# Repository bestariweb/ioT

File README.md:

# ioT
this Repository contain any tutorials for Arduino, Nodemcu and wemos device
You can find source code for respectively device on the folder by device name

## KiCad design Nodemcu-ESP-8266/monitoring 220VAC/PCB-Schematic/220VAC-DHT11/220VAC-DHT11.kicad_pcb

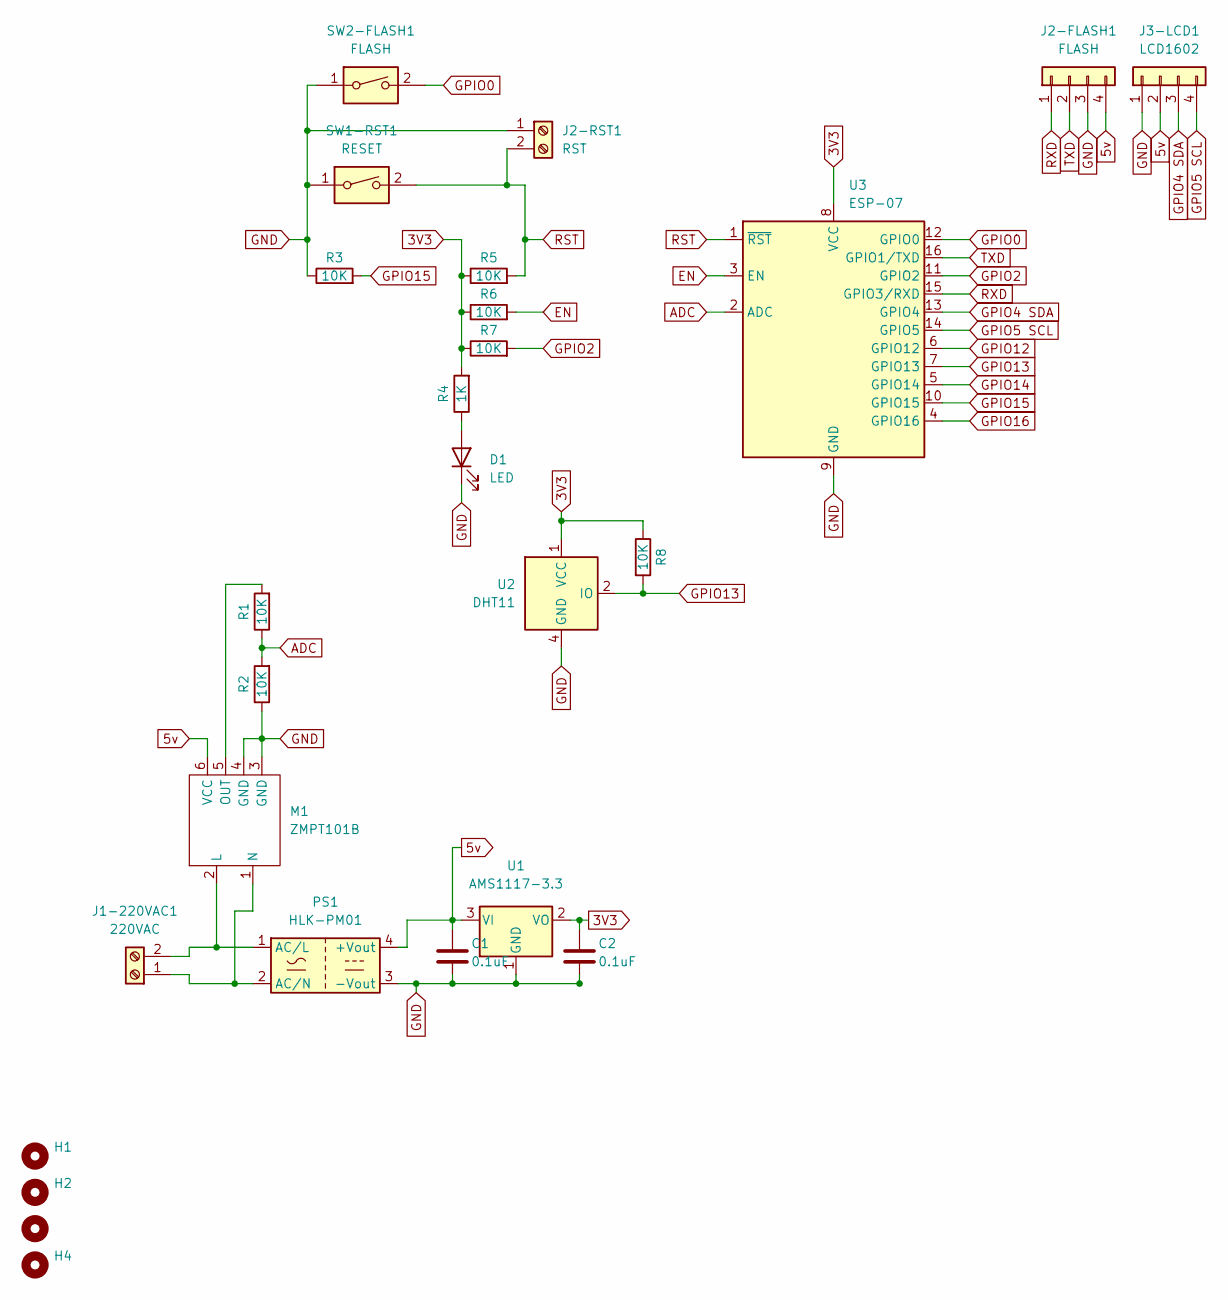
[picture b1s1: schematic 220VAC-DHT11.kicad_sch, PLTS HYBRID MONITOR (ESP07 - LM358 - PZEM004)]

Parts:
C1, C2: 0.1uF; C_1210_3225Metric
D1: LED; LED_D3.0mm_Clear
H1, H2, H3, H4: MountingHole_3.2mm_M3_ISO14580_Pad
J1-220VAC1: 220VAC; TerminalBlock_Phoenix_MKDS-1,5-2_1x02_P5.00mm_Horizontal
J2-FLASH1: FLASH; PinHeader_1x04_P2.54mm_Horizontal
J2-RST1: RST; TerminalBlock_Phoenix_PT-1,5-2-3.5-H_1x02_P3.50mm_Horizontal
J3-LCD1: LCD1602; PinHeader_1x04_P2.54mm_Vertical
M1: ZMPT101B; ZMPT101B_Module
PS1: HLK-PM01; Converter_ACDC_HiLink_HLK-PMxx
R1, R2, R3, R5, R6, R7, R8: 10K; R_1206_3216Metric_Pad1.30x1.75mm_HandSolder
R4: 1K; R_1206_3216Metric_Pad1.30x1.75mm_HandSolder
SW1-RST1: RESET; SW_PUSH_6mm_H7.3mm
SW2-FLASH1: FLASH; SW_PUSH_6mm_H7.3mm
U1: AMS1117-3.3; SOT-223-3_TabPin2
U2: DHT11; Aosong_DHT11_5.5x12.0_P2.54mm
U3: ESP-07

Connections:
3V3: C2.1, R4.2, R5.1, R6.1, R7.1, R8.1, U1.2 (VO), U2.1 (VCC), U3.8 (VCC)
5v: C1.1, J2-FLASH1.4, J3-LCD1.2, M1.6 (VCC), PS1.4 (+Vout), U1.3 (VI)
ADC: R1.1, R2.2, U3.2 (ADC)
EN: R6.2, U3.3 (EN)
GND: C1.2, C2.2, D1.1 (K), J2-FLASH1.3, J2-RST1.1, J3-LCD1.1, M1.3 (GND), M1.4 (GND), PS1.3 (-Vout), R2.1, R3.1, SW1-RST1.1, SW2-FLASH1.1, U1.1 (GND), U2.4 (GND), U3.9 (GND)
GPIO0: SW2-FLASH1.2, U3.12 (GPIO0)
GPIO2: R7.2, U3.11 (GPIO2)
GPIO4 SDA: J3-LCD1.3, U3.13 (GPIO4)
GPIO5 SCL: J3-LCD1.4, U3.14 (GPIO5)
GPIO12: U3.6 (GPIO12)
GPIO13: R8.2, U2.2 (IO), U3.7 (GPIO13)
GPIO14: U3.5 (GPIO14)
GPIO15: R3.2, U3.10 (GPIO15)
GPIO16: U3.4 (GPIO16)
unnamed: D1.2 (A), R4.1
unnamed: J1-220VAC1.1, M1.1 (N), PS1.2 (AC/N)
unnamed: J1-220VAC1.2, M1.2 (L), PS1.1 (AC/L)
unnamed: M1.5 (OUT), R1.2
RST: J2-RST1.2, R5.2, SW1-RST1.2, U3.1 (~RST)
RXD: J2-FLASH1.1, U3.15 (GPIO3/RXD)
TXD: J2-FLASH1.2, U3.16 (GPIO1/TXD)

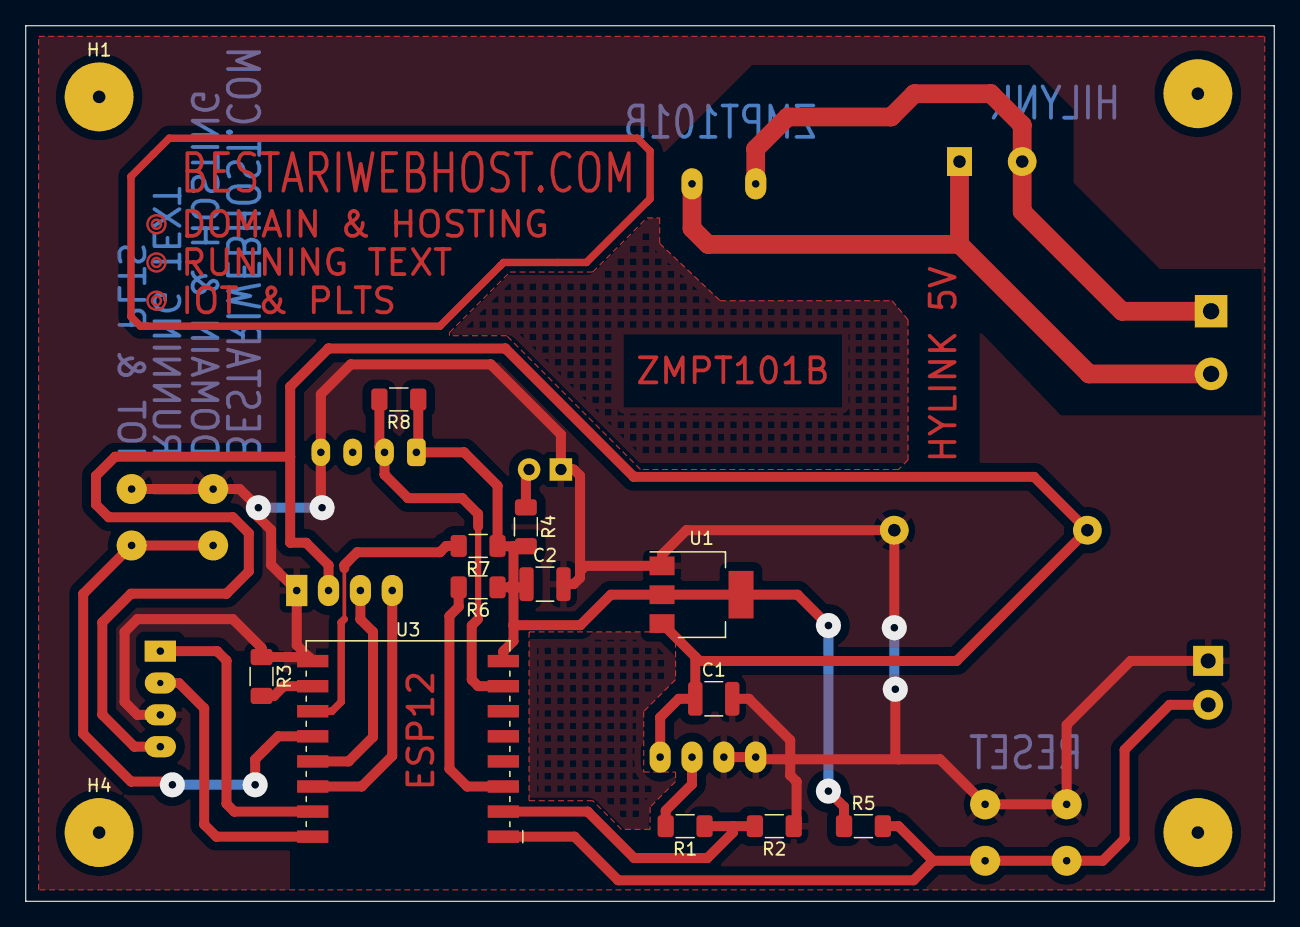
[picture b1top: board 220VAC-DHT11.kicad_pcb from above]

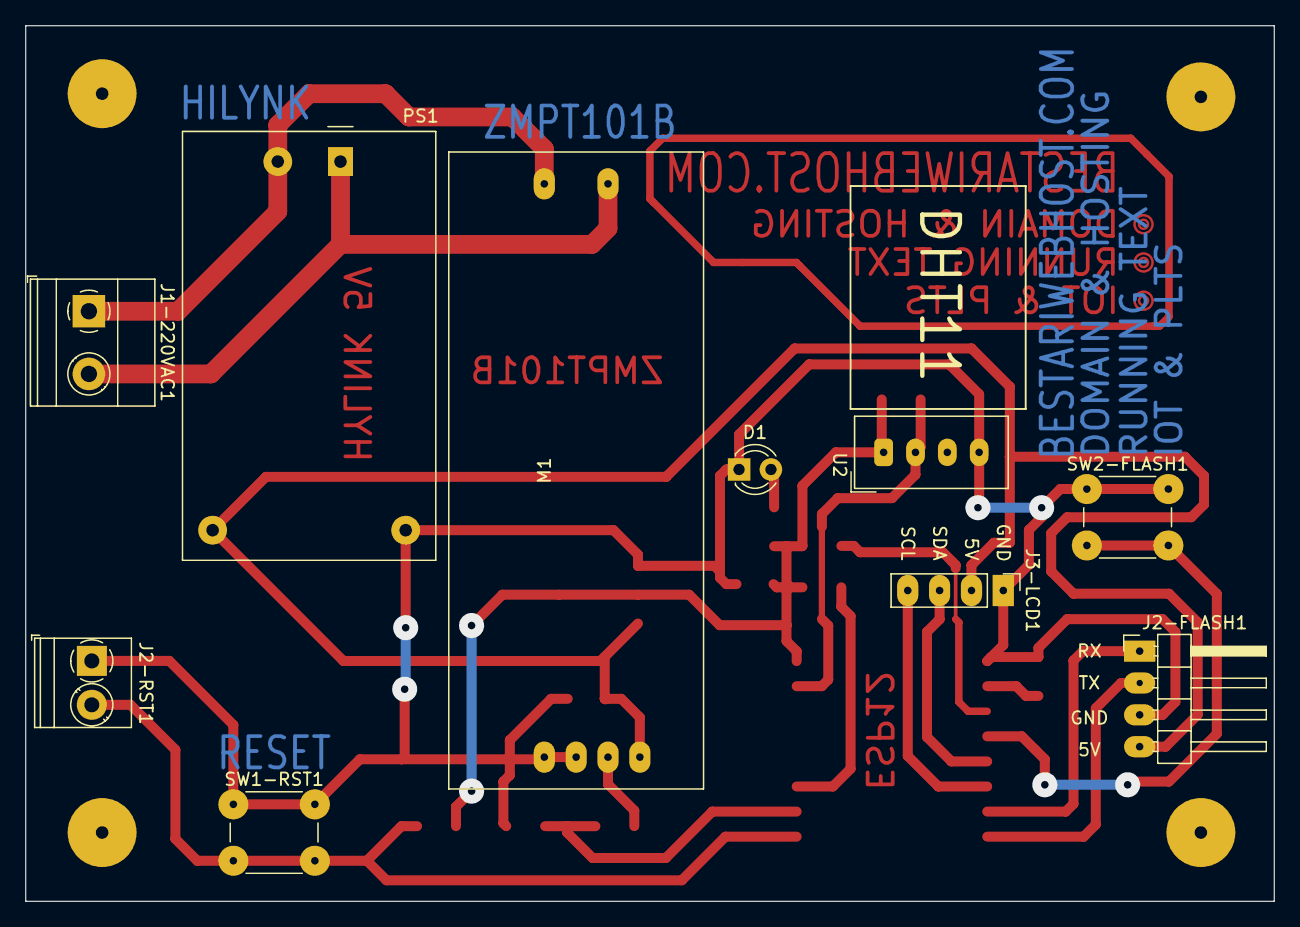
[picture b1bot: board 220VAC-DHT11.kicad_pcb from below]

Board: 2 copper layers, 99.6 x 69.8 mm, 26 parts (10 on the bottom side), 18 nets.

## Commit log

2021-08-11 README.md
    add description
2021-08-11 First Upload
2022-07-01 First Upload
    First Upload
